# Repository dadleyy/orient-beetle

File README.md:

# Orient-Beetle

A project that incorporates a wifi-enabled microcontroller, an e-ink display and some nice
RGB LEDs.

For general platform architecture documentation, see [`.docs/architecture.md`][arch].

For the hardware bill of materials, see [`.docs/hardware.md`][bom]

## Beetle PIO (Firmware)

The firmware for the application lives in [`src/beetle-pio`][fm-rd] and can be compiled
using the [platformIO cli][pio]. 

### Environment Setup: Redis Environment Variables

The firmware relies on compile-time configuration information to determine what server,
port, and authentication information to use when establishing it's secure connection to
your redis instance. The most straightforward way to set this up is to define a `.env`
file at the root of the `beetle-io` platformio application:

```
$ cat ./src/beetle-io/.env

REDIS_PORT=1234
REDIS_HOST="my-redis.my-host.com"
REDIS_AUTH_USERNAME="orient-beetle-device-id-consumer"
REDIS_AUTH_PASSWORD="1bc2ad"
```

This file is read by the [`extra_scripts`][extra_scripts] entry [`load_env.py`][lenv] and will
automatically attempt to set the correct `-DREDIS_HOST`, `-DREDIS_PORT`, and auth compiler flags.

The values of the `REDIS_AUTH_USERNAME` and `REDIS_AUTH_PASSWORD` values
require successfully "provisioning" your environment (more on this in the
[`srv` documentation](#beetle-srv-(web-backend)) below).

### Environment Setup: Redis Host CA Certificate

In order for the esp32 module to connect over tls to your redis host, you will need
to download the root ca certificate for the host and save it to:

```
src/beetle-pio/embeds/redis_host_root_ca.pem
```

The contents of this file are loaded into flash memory via the
`board_build.embed_txtfiles` setting defined in the project's `platform.ini`
file.

_For more information on how to prepare the ssl/tls components for our redis
connection, refer to [`.docs/redis-help.md`](.docs/redis-help.md)_.

### Compiling With `pio`

Once your environment and certificate file have been prepared, the firmware can
be compiled from the `beetle-pio` directory:

```
$ cd src/beetle-pio
$ pio run -t upload             <- will attempt to compile + upload to device
$ pio run -t upload -e release  <- builds without Serial logs
```

### Hardware & Documentation

For a list of harware involved and other documentation, see [`.docs/README.md`](/.docs/README.md).

#### Troubleshooting with `src/beetle-pio-tls-tester`

It can be ticky to know which certificate is required for a valid connection over tls with
your hosted redis provider. To help validate your certificate, the
[`src/beetle-pio-tls-tester`](./src/beetle-pio-tls-tester) directory contains a platformio
project can can be flashed onto your ESP32 to verify.

This project uses a very similar to configuration to the main `beetle-pio` project; you are
expected to provide both a `.env` file and `embeds/redis_host_root_ca.pem` file. If your
certificate file is valid, you should see something like:

```
[  4353][V][ssl_client.cpp:59] start_ssl_client(): Free internal heap before TLS 225035
[  4361][V][ssl_client.cpp:65] start_ssl_client(): Starting socket
[  4707][V][ssl_client.cpp:141] start_ssl_client(): Seeding the random number generator
[  4709][V][ssl_client.cpp:150] start_ssl_client(): Setting up the SSL/TLS structure...
[  4712][V][ssl_client.cpp:166] start_ssl_client(): Loading CA cert
[  4782][V][ssl_client.cpp:234] start_ssl_client(): Setting hostname for TLS session...
[  4783][V][ssl_client.cpp:249] start_ssl_client(): Performing the SSL/TLS handshake...
[  6214][V][ssl_client.cpp:270] start_ssl_client(): Verifying peer X.509 certificate...
[  6215][V][ssl_client.cpp:279] start_ssl_client(): Certificate verified.
[  6218][V][ssl_client.cpp:294] start_ssl_client(): Free internal heap after TLS 177751
[  6226][D][main.cpp:26] loop(): connection result: 1
[  7231][D][main.cpp:18] loop(): connected: 1
```

This assumes you have compiled and uploaded via `pio`:

```
$ pio run -t upload
$ screen /dev/ttyUSB0 115200
```

----

## Beetle SRV (Web Backend)

There are several rust exectuables that live in the [`srv/beetle-srv`](./src/beetle-srv/README.md)
directory. This includes the http api, a dirty little cli for troubleshooting, and a background worker
responsible for applying logic based on device connections. These applications generally require
an `env.toml` file with the various secrets that will be used for redis, mongo, etc... An example 
file can be seen at [`src/beetle-src/env.example.toml`](src/beetle-srv/env.example.toml)

For more detailed instructions for hosting your own instance, refer to [`.docs/hosting.md`](./.docs/hosting.md).

### Creating Redis ACL for all devices

As part of provisioning your environment, you will need to create the appropriate redis acl entry that
will be flashed onto all devices and should only be able to `pop` ids off our registrar index:

```
$ cd src/beetle-srv
$ cargo run cli provision orient-beetle-id-consumer abc1234
```

----

## Beetle UI (Web Frontend)

The web ui for this project can be found in the [`src/beetle-ui`](./src/beetle-ui/README.md) directory.

----

## Miscellaneous Tools

1. [WiFi Configuration HTML Generator][wchgen] - This tiny rust application is used to generate the
contents of the `src/beetle-pio/embed/index.html` file from an `index.html` file input.

--- 

## Nice Third Party Providers for Services Used At Runtime

- redis @ [upstash](https://upstash.com/) - supports tls _and_ `ACL` command management. not really free.
- mongo @ [cloud.mongodb.com](https://cloud.mongodb.com) - has a free tier for hosted mongodb databases/clusters.
- oauth @ [auth0](https://manage.auth0.com) - has a free tier for managing your login page.

---

This project was named by combining the name of the development board (fire<i>beetle</i>) with the name of
the manufacturer of the display being used (_orient_ displays).

[pio]: https://docs.platformio.org/en/stable/core/index.html
[dotenv]: https://github.com/ohmyzsh/ohmyzsh/blob/master/plugins/dotenv/dotenv.plugin.zsh
[wchgen]: ./tools/wchgen/README.md
[extra_scripts]: https://docs.platformio.org/en/latest/scripting/actions.html
[lenv]: ./src/beetle-pio/load_env.py
[fm-rd]: ./src/beetle-pio/README.md
[arch]: ./.docs/architecture.md
[bom]: ./.docs/hardware.md

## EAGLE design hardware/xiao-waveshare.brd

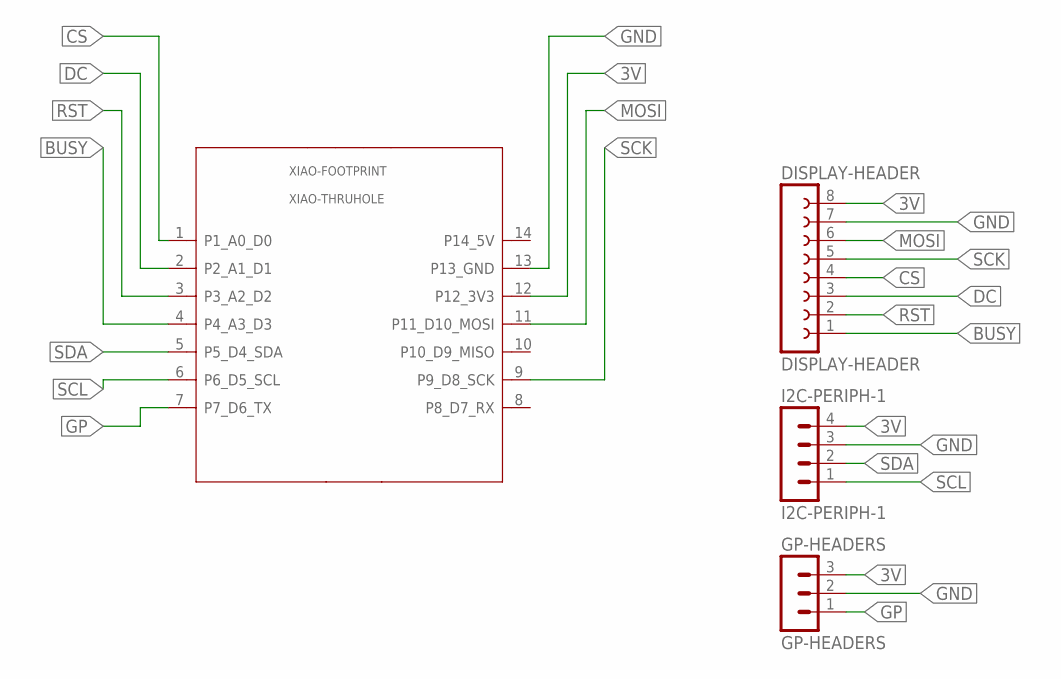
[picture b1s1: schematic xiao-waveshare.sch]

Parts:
DISPLAY-HEADER: DISPLAY-HEADER; FE08
GP-HEADERS: GP-HEADERS; MA03-1
I2C-PERIPH-1: I2C-PERIPH-1; MA04-1
XIAO-FOOTPRINT: XIAO-THRUHOLE; XIAO-GENERIC-THRUHOLE-MODULE14P-2.54-21X17.8MM

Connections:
3V: DISPLAY-HEADER.8, GP-HEADERS.3, I2C-PERIPH-1.4, XIAO-FOOTPRINT.12 (P12_3V3)
BUSY: DISPLAY-HEADER.1, XIAO-FOOTPRINT.4 (P4_A3_D3)
CS: DISPLAY-HEADER.4, XIAO-FOOTPRINT.1 (P1_A0_D0)
DC: DISPLAY-HEADER.3, XIAO-FOOTPRINT.2 (P2_A1_D1)
GND: DISPLAY-HEADER.7, GP-HEADERS.2, I2C-PERIPH-1.3, XIAO-FOOTPRINT.13 (P13_GND)
GP: GP-HEADERS.1, XIAO-FOOTPRINT.7 (P7_D6_TX)
MOSI: DISPLAY-HEADER.6, XIAO-FOOTPRINT.11 (P11_D10_MOSI)
RST: DISPLAY-HEADER.2, XIAO-FOOTPRINT.3 (P3_A2_D2)
SCK: DISPLAY-HEADER.5, XIAO-FOOTPRINT.9 (P9_D8_SCK)
SCL: I2C-PERIPH-1.1, XIAO-FOOTPRINT.6 (P6_D5_SCL)
SDA: I2C-PERIPH-1.2, XIAO-FOOTPRINT.5 (P5_D4_SDA)

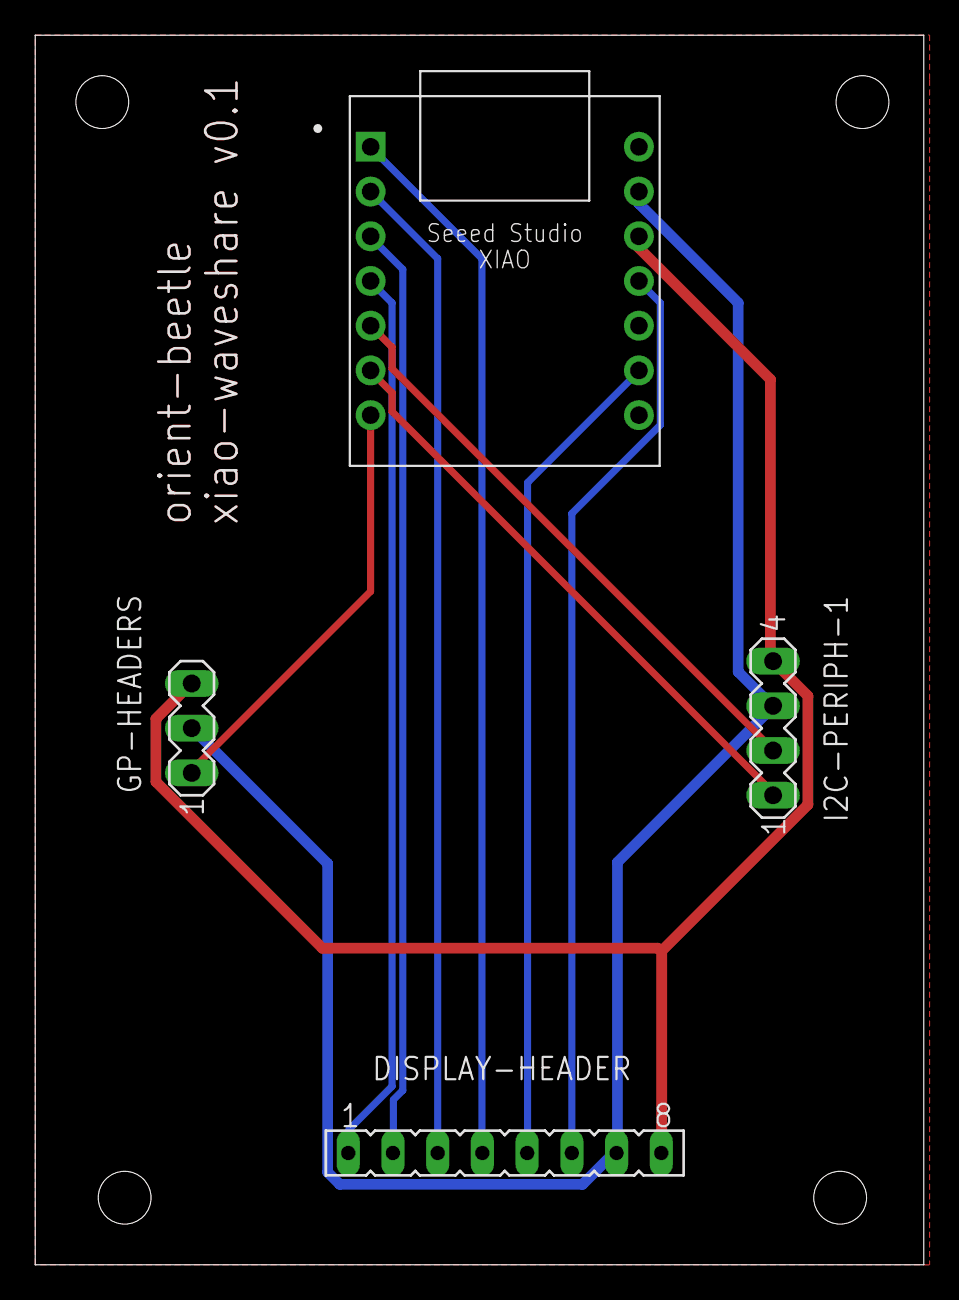
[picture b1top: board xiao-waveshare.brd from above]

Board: 2 copper layers, 50.5 x 69.8 mm, 4 parts (0 on the bottom side), 11 nets.

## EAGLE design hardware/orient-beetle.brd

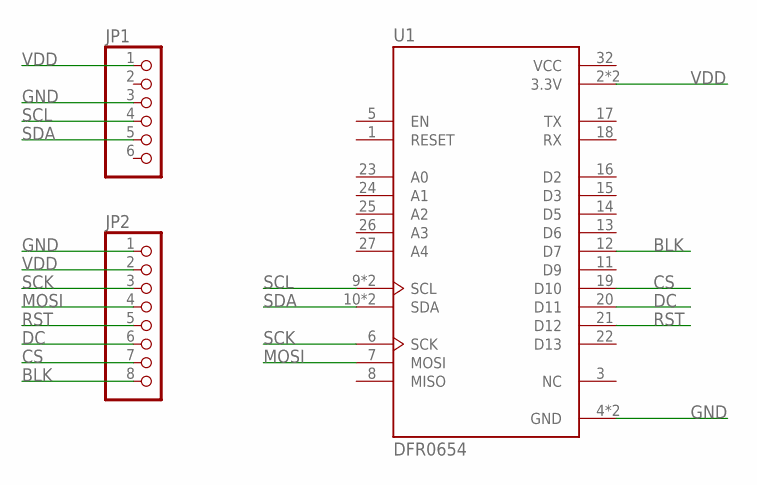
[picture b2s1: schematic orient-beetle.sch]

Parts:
JP1: PINHD-1X6; 1X06
JP2: PINHD-1X8; 1X08
U1: DFR0654; MODULE_DFR0654

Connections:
BLK: JP2.8, U1.12 (D7)
CS: JP2.7, U1.19 (D10)
DC: JP2.6, U1.20 (D11)
GND: JP1.3, JP2.1, U1.4 (GND), U1.30 (GND)
MOSI: JP2.4, U1.7 (MOSI)
RST: JP2.5, U1.21 (D12)
SCK: JP2.3, U1.6 (SCK)
SCL: JP1.4, U1.9 (SCL), U1.29 (SCL)
SDA: JP1.5, U1.10 (SDA), U1.28 (SDA)
VCC: U1.32 (VCC)
VDD: JP1.1, JP2.2, U1.2 (3.3V), U1.31 (3.3V)

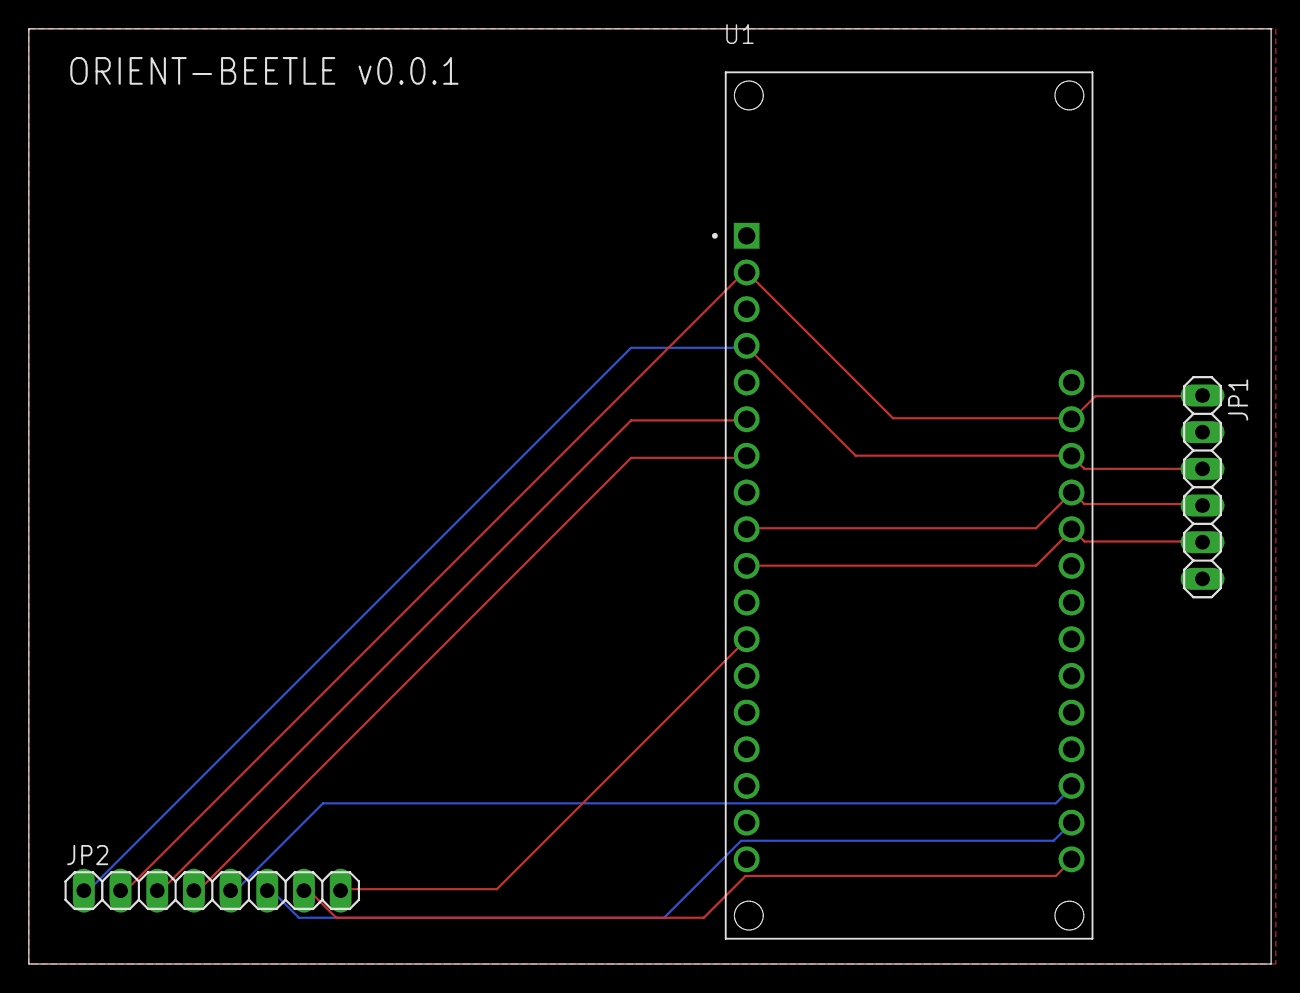
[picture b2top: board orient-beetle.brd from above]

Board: 2 copper layers, 86.0 x 64.8 mm, 3 parts (0 on the bottom side), 10 nets.

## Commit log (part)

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2022-05-07 minor cleanups
2022-05-07 engine-owned managers
2022-05-07 more frequent debugs
2022-05-07 saving
2022-05-07 driver update + display attempt
2022-05-07 id fixes and shorter for sanity
2022-05-07 start ui, ci
2022-05-07 add build steps to client
2022-05-07 add linting for kicks
2022-05-07 add forgotten cargo config for link
2022-05-07 fix ci/ui root location
2022-05-07 add some xhr to test/verify deployment
2022-05-07 fix and remove some linkds
2022-05-07 incorporate tailwind
2022-05-07 use target during test
2022-05-07 separate ci for non-cross build+test
2022-05-07 use github image
2022-05-07 ci and ui minimal (#3)
    * start ui, ci
    * quotefix
    * add build steps to client
    * add linting for kicks
    * add forgotten cargo config for link
    * ui artifact attempt
2022-05-08 hopefull cleaning up github actions triggering
2022-05-08 typo
2022-05-08 start to play with single publish job idea
2022-05-08 yaml format
2022-05-08 finish consolidation, hopefully
2022-05-08 maybe fix publish step
2022-05-08 glob release filename
2022-05-11 starting lotds of api work
2022-05-17 small wifi improvements, add reconnect attempt
2022-05-18 trudging through device ownership/claim ui
2022-05-18 more device registration work
2022-05-27 stopping point - device addition + removal
2022-06-09 move things around
2022-06-09 some more things
2022-06-09 fixing some things
2022-06-11 store more info in mongo
2022-06-11 initial impl of sending messages; woot
2022-06-11 fixing url pathing issue
2022-06-11 formatting
2022-06-11 small routing ui changes
2022-06-15 separate registration route
2022-06-17 cleanup up cli redis related things
2022-06-27 start work on redis ACL security for device registration
    The goal here is going to be to have the devices flashed with redis
    authentication information that can only blpop from the specific
    `ob:r` registrar index.
    Subsequent commands with be required to have authenticated using the id
    requested, which will have been locked down by the registar using an
    additional ACL entry.
2022-06-28 device-specific acls, :tada:
2022-06-28 add documentation for third party providers used
2022-07-10 initial pass at persistent creds
2022-07-10 display more device info
2022-07-10 node version bump for ci
2022-07-10 try a run command
2022-07-10 env filling
2022-07-10 more pio ci
2022-07-10 more pio ci stuff
2022-07-10 fix env typo
2022-07-10 play with maybe gpg
2022-07-10 retry
2022-07-10 gpg files in pio
2022-07-10 more gpg small changes
2022-07-10 path typo
2022-07-10 add pio artifact
2022-07-12 start mutli-message
2022-07-14 maybe better impl
2022-07-14 update github action ls
2022-07-14 add framework bin files
2022-07-14 multi message display (#1)
    * more mulit-message support
    * maybe better impl
    * update github action ls
    * update ls
    * add framework bin files
2022-07-15 initial screen case with sensor
2022-07-15 move sensor up more
2022-07-15 geometry nodes impl,sweet
2022-07-15 first pass at bottom
2022-07-15 geo-node increase screen hole y
2022-07-15 geo-nodes front +back
2022-07-15 going to print
2022-07-15 thicker, save
2022-07-15 starting v2
2022-07-15 more space for cord
2022-07-15 tiny adjustment - sensor closer to screen
2022-07-15 oops, flip
2022-07-15 adding rough eagle files
2022-07-15 rm caption
2022-07-16 make redis connection shared
2022-07-16 add basic updater code
2022-07-16 more work
2022-07-16 commenting things
2022-07-16 add logging to updater while downloading
2022-07-16 play with attempt to restart service
2022-07-16 add manual run control via api
2022-07-16 tarball that
2022-07-16 maybe short sha eh
2022-07-16 all short shas
2022-07-16 having fun with updater tool (#2)
    * add basic updater code
    * more work
    * fix updater artifact in ci
    * update compiler to rust 1.62
    * commenting things
    * add logging to updater while downloading
2022-07-17 minor fixes to updater
2022-07-17 use pathbuf more safe
2022-07-17 more updater cleanup
2022-07-17 correct updater interval logic
2022-07-17 another updater interval check for message
2022-07-20 add update mutex + api routes to updater
2022-07-21 redis connection fix + queued updater feature (#3)
    * adding connection retry on broken pipe
    * add update mutex + api routes to updater
2022-07-21 correct file update logic
2022-08-26 adding release notes to github action
2022-08-27 adding release notes to github action (#4)
2022-08-27 rm comment
2022-08-27 more logs for redis problems (#5)
    * more logs for redis problems
    * rm comment
2022-08-28 checking key before attempt
2022-08-28 logging more about redis problems
2022-08-28 fix workflow
2022-08-28 logging more about redis problems (#8)
2022-08-28 clippy for updater (#6)
    * clippy for updater
    * fix workflow
2022-08-28 only run osx ci on tags (#9)
2022-08-28 small pio debug changes
2022-08-30 small pio debug changes (#10)
    * small pio debug changes
    * more beetle-pio updates
2022-08-30 updating kramer for better diagnostics
2022-08-30 updating kramer for better diagnostics (#11)
2022-08-31 finalizing kramer update (#12)
2022-08-31 small cppcheck imrovement, maybe
2022-08-31 updating cargo deps
2022-08-31 retry on all error kinds
2022-08-31 remove default features, maybe compile time improve
2022-09-08 minor logging improvements/tweaks
2022-09-08 some cargo updates
2022-09-08 minor changes to logs + dependencies (#15)
    * remove default features, maybe compile time improve
    * minor logging improvements/tweaks
    * clippy
    * some cargo updates
2022-09-08 display driver changes
2022-09-10 redis improvements, hopefully
2022-09-10 nitpick
2022-09-10 more font changes
2022-09-10 pio redis + graphics changes (#17)
    * redis improvements, hopefully
    * saving
    * nitpick
    * font updates
    * more font changes
2022-09-12 adding logout (#18)
2022-09-14 thicker
2022-09-14 big reset; new pcb layout
2022-09-14 taller beetle bit
2022-09-14 moving proxomity gap
2022-09-14 bigger and more holes
2022-09-14 another prox hole attempt
2022-09-14 smaller screw holes:
2022-09-14 checking in fusion stuff
2022-09-14 saving minor changes
2022-09-14 tiny tiny changes
2022-09-14 prox hole adjust
2022-09-14 total enclosure attempt
2022-09-14 add bundled thing
2022-09-14 last minute deeper
2022-09-14 some changes
2022-09-14 maybe some things
2022-09-14 here we go again
2022-09-14 merging latest hardware (#19)
    * initial screen case with sensor
    * solidify(4) too much, back to 3
    * move sensor up more
    * first pass at bottom
    * smaller holes, 0.667 of 3.6 diameter = 2.40
    * geometry nodes impl,sweet
2022-10-01 add image
2022-10-01 some ui login page changes
2022-10-11 rm gcode
2023-04-12 [wip] starting work on xiao esp32c3 eink
2023-04-12 [wip] updating pio
2023-04-12 [wip] update kramer, pio xiao platform set
2023-04-13 [wip] image update
2023-04-13 [wip] prepare subdir for artifact
2023-04-13 [wip] small changes to load_env
2023-04-13 [wip] ci workflow formatting
2023-04-13 [wip] ci diagnostics
2023-04-13 [wip] ci: fix instruction path, try boot_app0.bin again
2023-04-13 [wip] ci: fix missing newline escape
2023-04-14 [wip] lots of redis things
2023-04-14 [wip] renaming things
2023-04-14 [wip] pio check fixes
2023-04-15 [wip] minor cleanups
2023-04-19 [wip] saving work
2023-04-19 [wip] startin to parse messages as png
2023-04-20 [wip] fix github artifact names
2023-04-20 [wip] native -> rgb565
2023-04-25 [wip] starting rendering queue architecture
2023-04-25 [wip] adding initial renderer worker + script
2023-04-25 [wip] bundle script fix
2023-04-25 [wip] pathing change for bundle script
2023-04-26 [wip] using queue for device api
2023-05-02 [wip] work in progress development mock
2023-05-05 [wip] saving images from mock device
2023-05-09 [wip] fixing the device page a bit
2023-05-09 [wip] misc cleanup in pio
2023-05-10 [wip] minor workflow naming changes
2023-05-10 [wip] fix job names
2023-05-10 [wip] try out rust-cache
2023-05-10 [wip] more caching
2023-05-10 [wip] another go at github publish steps
2023-05-10 [wip] correct artifact name
2023-05-10 [wip] ui artifact to s3 too
2023-05-10 [wip] update mongo diagnostics in renderer
2023-05-10 [wip] adding clap to main web worker cli
2023-05-11 [wip] print version on startup
2023-05-11 porting to xiao + e-ink (#21)
    * [wip] starting work on xiao esp32c3 eink
    * [wip] update pio ci instructions
    * [wip] updating pio
    * [wip] update kramer, pio xiao platform set
    * [wip] image update
    * [wip] ci formatting
2023-05-11 update bom-related documentation
2023-05-12 [wip] just having some fun with lighting
2023-05-16 [wip] impl lighting disable/enable fw
2023-05-16 [wip] flushing out queue api again
2023-05-19 [wip] adds qr code rendering support
2023-05-19 [wip] updating ui to support links
2023-05-19 [wip] a tiny little responsive change
2023-05-20 [wip] add shortpath to registration via scannable
2023-05-20 [wip] clippy lints
2023-05-20 [wip] ui fix
2023-05-20 [wip] publish srv docs to aws
2023-05-22 [wip] jobbing-up the things
2023-05-24 [wip] misc ui improvements
2023-05-24 [wip] cleaning up unused ui code
2023-05-24 [wip] try fixing ci paths for workspace
2023-05-24 [wip] rm updater; deployment method changed.
2023-05-27 [wip] filling out more rename functionality
2023-05-27 [wip] sending welcome back
2023-05-27 [wip] first crappy pass at toggle auth model
2023-05-27 [wip] lint fix
2023-05-27 [wip] maybe led fix
2023-05-31 [wip] playing around with more advanced layouts
2023-06-07 [wip] saving
2023-06-10 [wip] token rotation
2023-06-10 [wip] moving to message from rename after submit
2023-06-10 [wip] update cookie unset flags
2023-06-10 [wip] starting scheduling api
2023-06-10 [wip] authority state transitions
2023-06-12 [wip] starting api/jobs of scheduling
2023-06-12 [wip] more schedule rendering prep
2023-06-26 [wip] more rendering updates
2023-06-26 [wip] pull history off diagnostics
2023-06-26 [wip] use default for font
2023-06-26 [wip] render more events
2023-06-28 minor pio related changes; reduce memory use
2023-07-01 authorities, schedules, histories (#23)
2023-07-01 types -> schema
2023-07-04 starting state render percolation
2023-07-04 impl push
2023-07-06 cargo updates
2023-07-06 move mock into separate package, start ui
2023-07-06 minor ui improvements
2023-07-08 persistent device rendering state (#24)
    * types -> schema
    * starting state render percolation
    * impl push
    * flushing out more state rendering/mutation
    * cargo updates
    * move mock into separate package, start ui
2023-07-08 [hw] more hardware updates (#25)
2023-07-19 some minor cleanups for sanity. named enums
2023-07-20 start migrations, maybe
2023-07-20 migration cleanup
2023-07-20 more cleanup
2023-07-20 adding helpful logs to migration
2023-07-20 ui footer change
2023-07-21 try adding some more logging for help
2023-07-21 loggin tweaks
2023-07-31 debug -> trace in google logs
2023-08-02 tiny newrelic reporting; job queue length
2023-08-02 dependency updates + root cleanup
2023-08-03 passing at job debounce/throttle
2023-08-03 diagnostic ingestion event
2023-08-22 schema changes (#26)
    * [ci] fix workflow gpg
    * some minor cleanups for sanity. named enums
    * start migrations, maybe
    * device state migration too
    * migration cleanup
    * more cleanup
2023-08-22 [hw] adding an attempt at a little locking
    [hw] more filets
    latest stl files
2023-08-30 [hw] adding an attempt at a little locking (#27)
    [hw] more filets
    latest stl files
2023-10-31 start route cleanup
2023-10-31 try add toolchain
2023-10-31 fileinput accept attribute
2023-10-31 ci fixes
2023-11-01 warn on file size
2023-11-01 larger max file limit
2023-11-05 filling in initial auth
2023-11-06 rm unused lib files
2023-11-06 image upload support (#28)
    * [cargo] updates
    * try add toolchain
    * start route cleanup
    * start raw image upload + rendering
    * fileinput accept attribute
    * saving
2024-01-03 login page update + better error on boot for bad srv config
2024-01-06 fsm wifi event stabilization
2024-01-06 more diagnostic logging for job queueing
2024-01-06 try playing with merge_bins
2024-01-06 add a version string to common logs
2024-01-09 add reminder, fix ca in CI
2024-01-09 quoted host ca
2024-01-18 configuring lighting, destructor fix, addr printing
2024-03-31 terminate server before global ap disconnect
